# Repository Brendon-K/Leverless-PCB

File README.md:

# Leverless PCB

Footprint Sources
- Hotswaps: https://github.com/daprice/keyswitches.pretty
- Pico: https://www.snapeda.com/parts/RASPBERRY%20PI%20PICO%20W/Raspberry%20Pi/view-part
- Switch: https://www.snapeda.com/parts/MX1A-11NN/Cherry/view-part

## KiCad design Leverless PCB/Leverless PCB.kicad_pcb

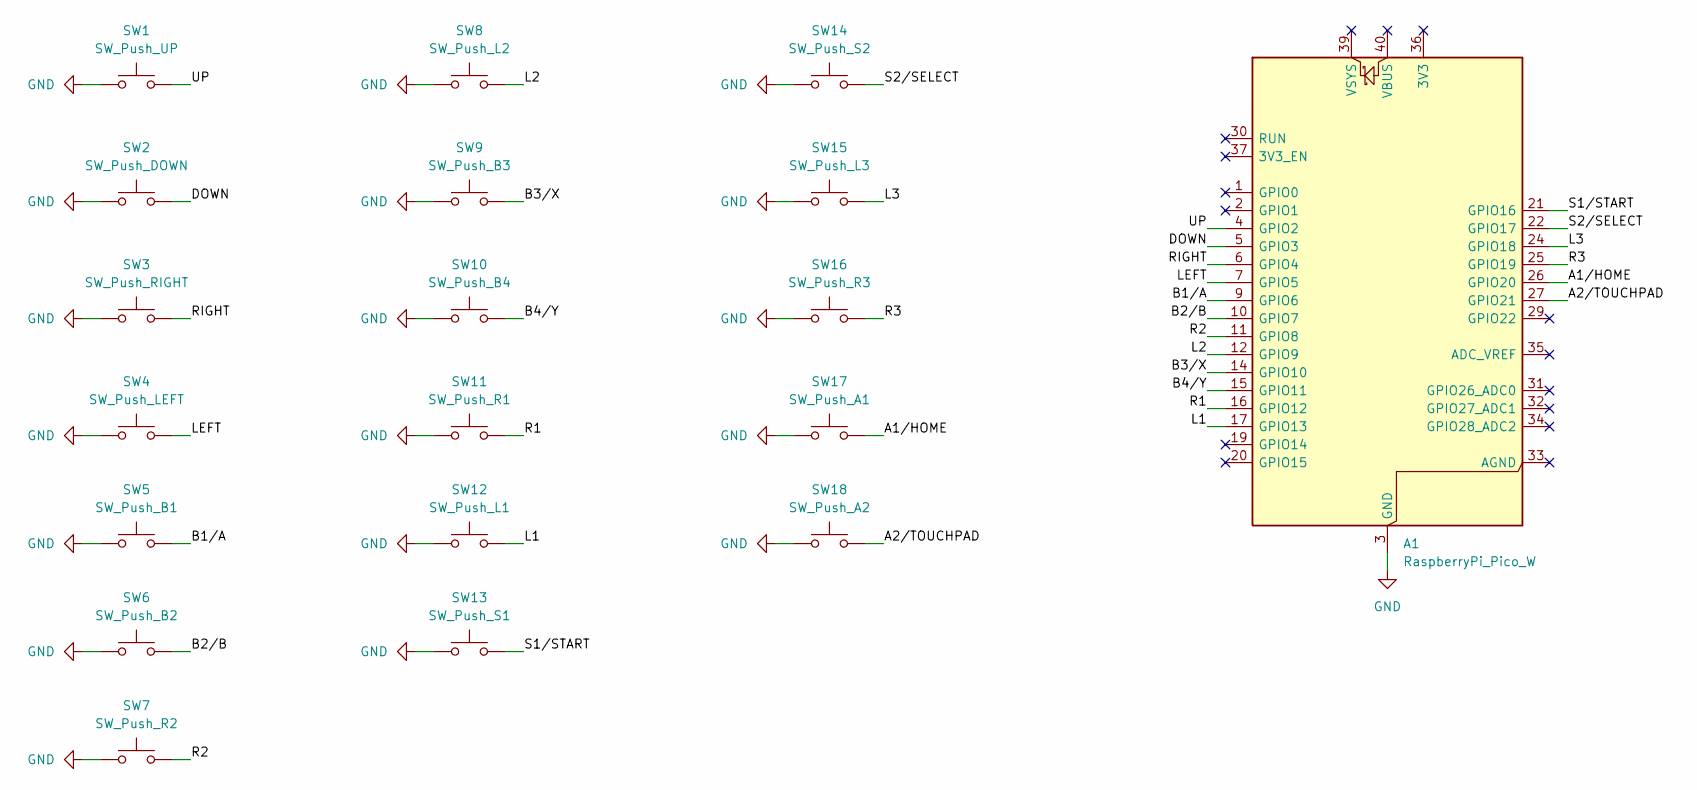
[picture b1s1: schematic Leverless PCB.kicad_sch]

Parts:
A1: RaspberryPi_Pico_W; RaspberryPi_Pico_Common_Unspecified
SW1: SW_Push_UP; Kailh_socket_MX_platemount
SW2: SW_Push_DOWN; Kailh_socket_MX_platemount
SW3: SW_Push_RIGHT; Kailh_socket_MX_platemount
SW4: SW_Push_LEFT; Kailh_socket_MX_platemount
SW5: SW_Push_B1; Kailh_socket_MX_platemount
SW6: SW_Push_B2; Kailh_socket_MX_platemount
SW7: SW_Push_R2; Kailh_socket_MX_platemount
SW8: SW_Push_L2; Kailh_socket_MX_platemount
SW9: SW_Push_B3; Kailh_socket_MX_platemount
SW10: SW_Push_B4; Kailh_socket_MX_platemount
SW11: SW_Push_R1; Kailh_socket_MX_platemount
SW12: SW_Push_L1; Kailh_socket_MX_platemount
SW13: SW_Push_S1; Kailh_socket_MX_platemount
SW14: SW_Push_S2; Kailh_socket_MX_platemount
SW15: SW_Push_L3; Kailh_socket_MX_platemount
SW16: SW_Push_R3; Kailh_socket_MX_platemount
SW17: SW_Push_A1; Kailh_socket_MX_platemount
SW18: SW_Push_A2; Kailh_socket_MX_platemount

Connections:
/A1/HOME: A1.26 (GPIO20), SW17.2
/A2/TOUCHPAD: A1.27 (GPIO21), SW18.2
/B1/A: A1.9 (GPIO6), SW5.2
/B2/B: A1.10 (GPIO7), SW6.2
/B3/X: A1.14 (GPIO10), SW9.2
/B4/Y: A1.15 (GPIO11), SW10.2
/DOWN: A1.5 (GPIO3), SW2.2
/L1: A1.17 (GPIO13), SW12.2
/L2: A1.12 (GPIO9), SW8.2
/L3: A1.24 (GPIO18), SW15.2
/LEFT: A1.7 (GPIO5), SW4.2
/R1: A1.16 (GPIO12), SW11.2
/R2: A1.11 (GPIO8), SW7.2
/R3: A1.25 (GPIO19), SW16.2
/RIGHT: A1.6 (GPIO4), SW3.2
/S1/START: A1.21 (GPIO16), SW13.2
/S2/SELECT: A1.22 (GPIO17), SW14.2
/UP: A1.4 (GPIO2), SW1.2
GND: A1.3 (GND), A1.8 (GND), A1.13 (GND), A1.18 (GND), A1.23 (GND), A1.28 (GND), A1.38 (GND), SW1.1, SW2.1, SW3.1, SW4.1, SW5.1, SW6.1, SW7.1, SW8.1, SW9.1, SW10.1, SW11.1, SW12.1, SW13.1, SW14.1, SW15.1, SW16.1, SW17.1, SW18.1

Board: 2 copper layers, 19 parts (0 on the bottom side), 19 nets, no tracks yet.
